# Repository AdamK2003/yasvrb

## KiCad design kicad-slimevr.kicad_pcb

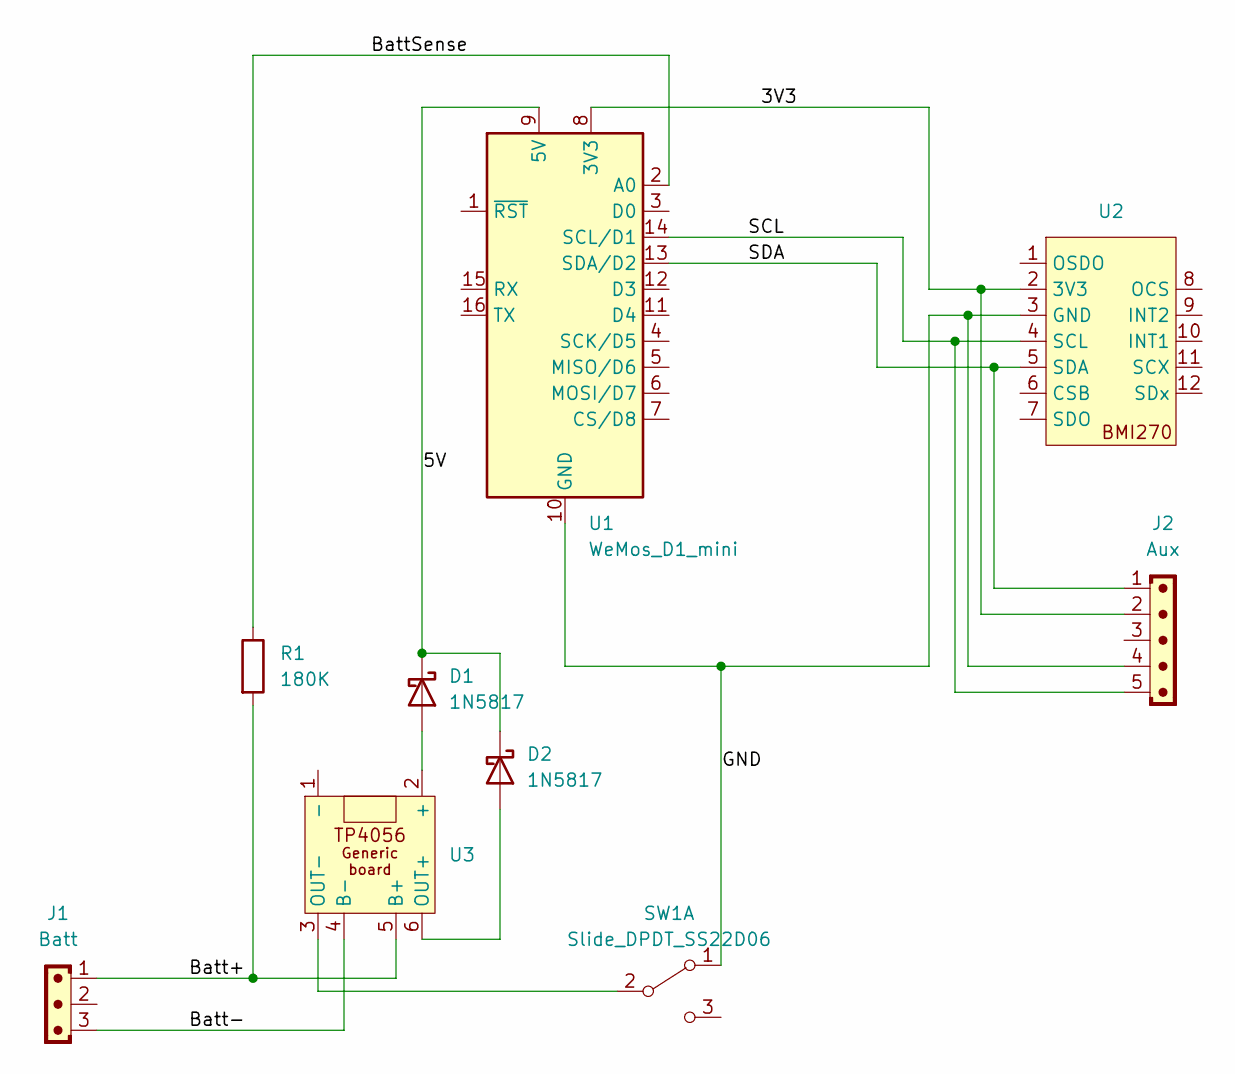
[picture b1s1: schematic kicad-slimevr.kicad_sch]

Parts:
D1, D2: 1N5817; D_DO-41_SOD81_P10.16mm_Horizontal
J1: Batt; JST_PH_S3B-PH-K_1x03_P2.00mm_Horizontal
J2: Aux; JST_XH_S5B-XH-A-1_1x05_P2.50mm_Horizontal
R1: 180K; R_Axial_DIN0207_L6.3mm_D2.5mm_P10.16mm_Horizontal
SW1: Slide_DPDT_SS22D06; SW_Slide_SPDT_Angled_CK_OS102011MA1Q; Part Number SS22D06
U1: WeMos_D1_mini; WEMOS_D1_mini_light
U2: BMI270 KOUNOLAB DevBoard
U3: TP4056_Generic_PCB

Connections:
/3V3: J2.2, U1.8 (3V3), U2.2 (3V3)
/5V: D1.1 (K), D2.1 (K), U1.9 (5V)
/Batt+: J1.1, R1.2, U3.5 (B+)
/Batt-: J1.3, U3.4 (B-)
/BattSense: R1.1, U1.2 (A0)
/GND: J2.4, SW1.1 (A), U1.10 (GND), U2.3 (GND)
/SCL: J2.5, U1.14 (SCL/D1), U2.4 (SCL)
/SDA: J2.1, U1.13 (SDA/D2), U2.5 (SDA)
unnamed: D1.2 (A), U3.2 (+)
unnamed: D2.2 (A), U3.6 (OUT+)
unnamed: SW1.2 (B), U3.3 (OUT-)

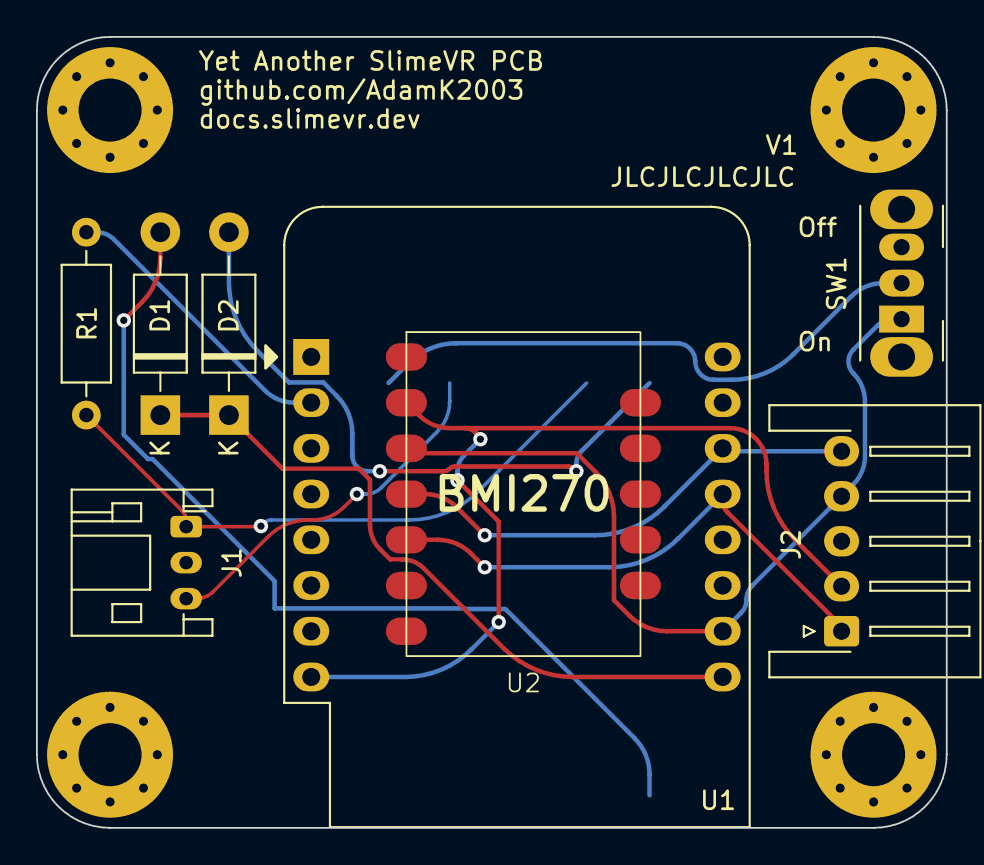
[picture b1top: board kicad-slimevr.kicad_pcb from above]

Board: 2 copper layers, 50.5 x 43.9 mm, 9 parts (1 on the bottom side), 11 nets.

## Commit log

2024-04-16 big bang
